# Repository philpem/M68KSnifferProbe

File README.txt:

M68000 DIP sniffer probe for use with HP 16700 series logic analysers

Phil Pemberton M0OFX, March 2019

Wiring is as per the HP E2447A sniffer probe, but altered for DIP instead
of PGA pinout.

Requires four off 20pin IDC headers to mate with four HP 01650-63203
transition adapters. These then connect to the LA's woven pod cables.

**** CAUTION - BUG! ****
You will need to mount the two outside headers (in the row of three) at a slight angle, otherwise
the rivets which hold the adapters together will stop you from plugging them all in.

One way to do this is as follows:

  * Solder in the centre header and plug a transition adapter into it.
  * Plug a transition adapter into a fresh, unsoldered header.
  * Push that header into the PCB and make sure the rivets on the adapters have some clearance.
  * Solder in one pin of the header. Check fit and function.
  * Repeat for the other outside header.
  * Solder another diagonally opposite pin
  * Check one last time that the plugs clear each other. Melt solder and adjust if needed.
  * When you're absolutely sure, solder the remaining pins.
  
This should leave you with a usable trnsition adapter.
**** CAUTION - BUG! ****

Connection to the host 68K processor is made by soldering two rows of mating
0.1in (2.54mm) pitch headers to the CPU pins and the bottom of the probe.
This allows the probe to be disconnected from the 68K if needed.
Pins should be used on the 68K and sockets on the probe -- this allows LA
probes and scope probes to be connected directly to the 68K if needed.

Either square-pin or turned-pin headers may be used.

Information sources:

HP E2447-97002 probe adapter documentation, p. 66-68.	http://literature.cdn.keysight.com/litweb/pdf/E2447-97002.pdf

HP 01650-63203 transition adapter pinout				https://www.keysight.com/main/editorial.jspx?ckey=553886&id=553886&nid=-11143.0.00&lc=eng&cc=GB

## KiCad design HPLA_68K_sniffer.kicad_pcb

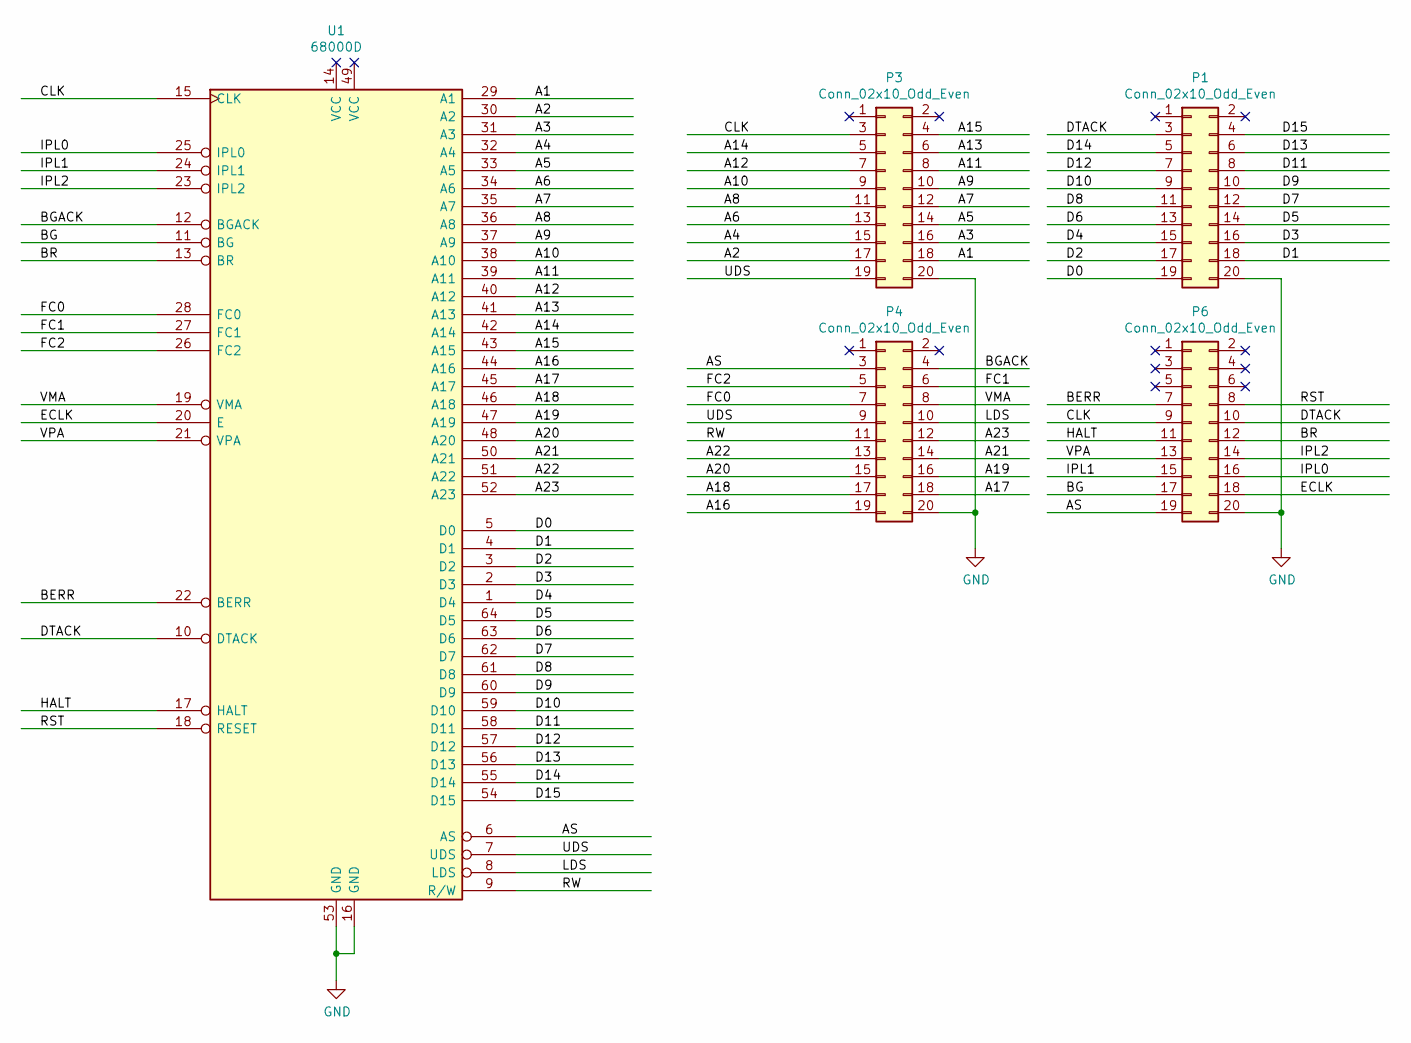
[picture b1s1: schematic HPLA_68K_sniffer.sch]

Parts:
P1, P3, P4, P6: Conn_02x10_Odd_Even; IDC-Header_2x10_P2.54mm_Vertical
U1: 68000D; DIP-64_W22.86mm_LongPads

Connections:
/A1: P3.18, U1.29 (A1)
/A2: P3.17, U1.30 (A2)
/A3: P3.16, U1.31 (A3)
/A4: P3.15, U1.32 (A4)
/A5: P3.14, U1.33 (A5)
/A6: P3.13, U1.34 (A6)
/A7: P3.12, U1.35 (A7)
/A8: P3.11, U1.36 (A8)
/A9: P3.10, U1.37 (A9)
/A10: P3.9, U1.38 (A10)
/A11: P3.8, U1.39 (A11)
/A12: P3.7, U1.40 (A12)
/A13: P3.6, U1.41 (A13)
/A14: P3.5, U1.42 (A14)
/A15: P3.4, U1.43 (A15)
/A16: P4.19, U1.44 (A16)
/A17: P4.18, U1.45 (A17)
/A18: P4.17, U1.46 (A18)
/A19: P4.16, U1.47 (A19)
/A20: P4.15, U1.48 (A20)
/A21: P4.14, U1.50 (A21)
/A22: P4.13, U1.51 (A22)
/A23: P4.12, U1.52 (A23)
/AS: P4.3, P6.19, U1.6 (AS)
/BERR: P6.7, U1.22 (BERR)
/BG: P6.17, U1.11 (BG)
/BGACK: P4.4, U1.12 (BGACK)
/BR: P6.12, U1.13 (BR)
/CLK: P3.3, P6.9, U1.15 (CLK)
/D0: P1.19, U1.5 (D0)
/D1: P1.18, U1.4 (D1)
/D2: P1.17, U1.3 (D2)
/D3: P1.16, U1.2 (D3)
/D4: P1.15, U1.1 (D4)
/D5: P1.14, U1.64 (D5)
/D6: P1.13, U1.63 (D6)
/D7: P1.12, U1.62 (D7)
/D8: P1.11, U1.61 (D8)
/D9: P1.10, U1.60 (D9)
/D10: P1.9, U1.59 (D10)
/D11: P1.8, U1.58 (D11)
/D12: P1.7, U1.57 (D12)
/D13: P1.6, U1.56 (D13)
/D14: P1.5, U1.55 (D14)
/D15: P1.4, U1.54 (D15)
/DTACK: P1.3, P6.10, U1.10 (DTACK)
/ECLK: P6.18, U1.20 (E)
/FC0: P4.7, U1.28 (FC0)
/FC1: P4.6, U1.27 (FC1)
/FC2: P4.5, U1.26 (FC2)
/HALT: P6.11, U1.17 (HALT)
/IPL0: P6.16, U1.25 (IPL0)
/IPL1: P6.15, U1.24 (IPL1)
/IPL2: P6.14, U1.23 (IPL2)
/LDS: P4.10, U1.8 (LDS)
/RST: P6.8, U1.18 (RESET)
/RW: P4.11, U1.9 (R/W)
/UDS: P3.19, P4.9, U1.7 (UDS)
/VMA: P4.8, U1.19 (VMA)
/VPA: P6.13, U1.21 (VPA)
GND: P1.20, P3.20, P4.20, P6.20, U1.16 (GND), U1.53 (GND)

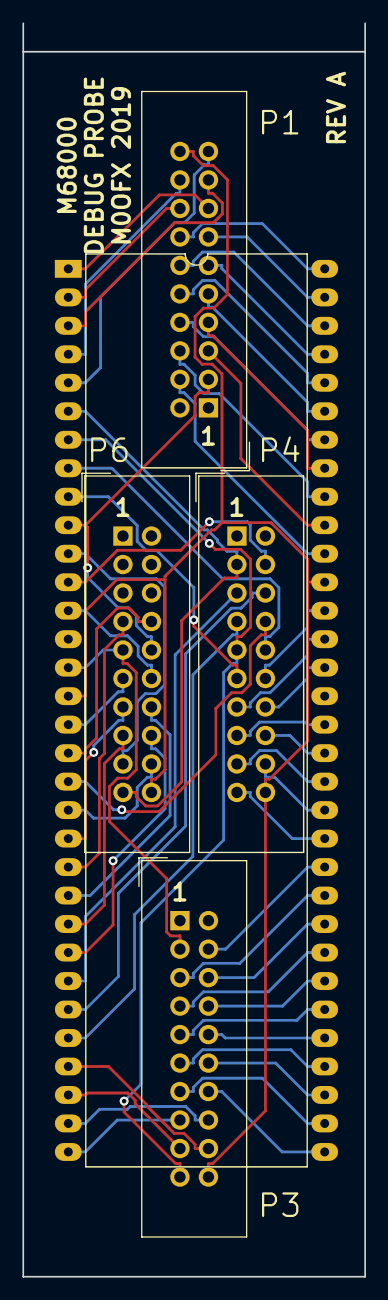
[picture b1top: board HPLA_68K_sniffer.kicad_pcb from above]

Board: 2 copper layers, 30.5 x 111.8 mm, 5 parts (0 on the bottom side), 61 nets.

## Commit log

2019-05-20 Update README -- document known bug
